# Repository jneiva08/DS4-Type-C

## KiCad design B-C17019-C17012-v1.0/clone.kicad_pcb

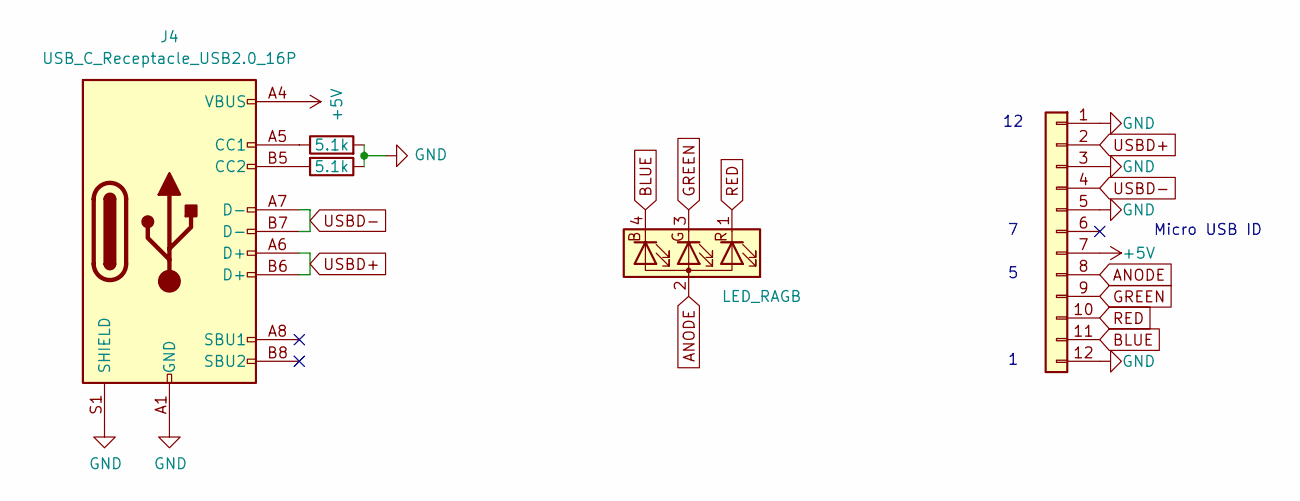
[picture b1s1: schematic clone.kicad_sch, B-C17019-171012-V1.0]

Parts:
D1: LED_RAGB; FM-3510RGBA-SG
J3: Conn_01x12; FPC_Connector
J4: USB_C_Receptacle_USB2.0_16P; USB_C
R3, R4: 5.1k; R_0603_1608Metric_Pad0.98x0.95mm_HandSolder

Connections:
+5V: J3.7, J4.A4 (VBUS), J4.A9 (VBUS), J4.B4 (VBUS), J4.B9 (VBUS)
ANODE: D1.2 (A), J3.8
BLUE: D1.4 (BK), J3.11
GND: J3.1, J3.3, J3.5, J3.12, J4.A1 (GND), J4.A12 (GND), J4.B1 (GND), J4.B12 (GND), J4.S1 (SHIELD), R3.1, R4.2
GREEN: D1.3 (GK), J3.9
unnamed: J4.A5 (CC1), R4.1
unnamed: J4.B5 (CC2), R3.2
RED: D1.1 (RK), J3.10
USBD+: J3.2, J4.A6 (D+), J4.B6 (D+)
USBD-: J3.4, J4.A7 (D-), J4.B7 (D-)

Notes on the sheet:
Micro USB ID

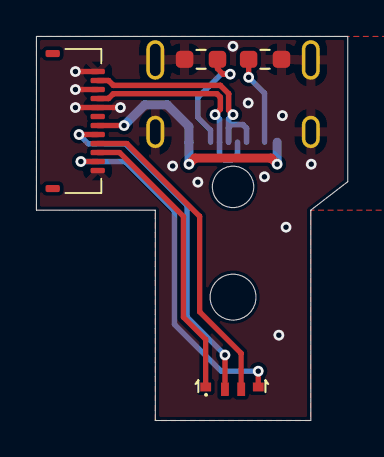
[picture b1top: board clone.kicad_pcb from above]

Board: 2 copper layers, 17.3 x 21.3 mm, 5 parts (1 on the bottom side), 10 nets.

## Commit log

2026-01-18 Add circuit for a non official PS4 controller
